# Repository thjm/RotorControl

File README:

$Id: README,v 1.8 2014/03/23 08:37:47 mathes Exp $

README file for Projekte/RotorControl
-----------------------------------------------------------------------------

This is the README file for the rotator controller project.

Directories:
-------------

- Bootloader : contains the boot loeader for the antenna sensor uC

- Docu : various documentation files

- DisplayUR : parts takes from Ulrich Radig's (http://www.ulrichradig.de)
          PowerSupply project. The display unit presented there seems to be
          quite usable for a simple display here, just software needs to be 
          adopted.

- Eagle : contains drawings and schemes done with the Eagle layout program

- Linux : various test programs, to be run on Linux

- LSM303 : library and example for the Pololu LSM303DLH 6-axis sensor
          breakout board. The boards contains a 3-axis magnetometer and a
          3-axis accelerometer.
          See also:
          - http://www.lipoly.de/index.php?main_page=product_info&products_id=165628
          - data sheet LSM303DLH.pdf
          - LSM303DLH-compass-app-note.pdf
          - LSM303DLH-orangutan-example-cde.zip
          - UM10204.pdf (I2C-bus specification)
          - https://github.com/ryantm/LSM303DLH (Arduino library)

- Test : directory containing various test programs for the 'rotorcontrol'
         hardware environment

Project layout (Rev. 1.1)
-------------------------

- the display of UR's PS1 project will be used to display the current and the
  set value for the azimuth (directory DisplayUR)

- a LSM303DLH accelerometer and compass module will be used to determine the
  antenna direction. It will be coupled to the main electronics via a serial
  interface (coupled via RS-485)

- the main electronics module has the task to
  - receive direction information from the LSM303DLH
  - calculate/average the direction information and send it to the display 
    module
  - compare the current direction with the preset value and pass this
    information to the rotator controller (software module)
  - switch the rotator motor in an appropriate way to achieve the desired
    direction; handle (optional) end-switches and a clutch/brake
  - get users input via push buttons (attached to the main electronics or to
    the display module?)
  - ...

=============================================================================

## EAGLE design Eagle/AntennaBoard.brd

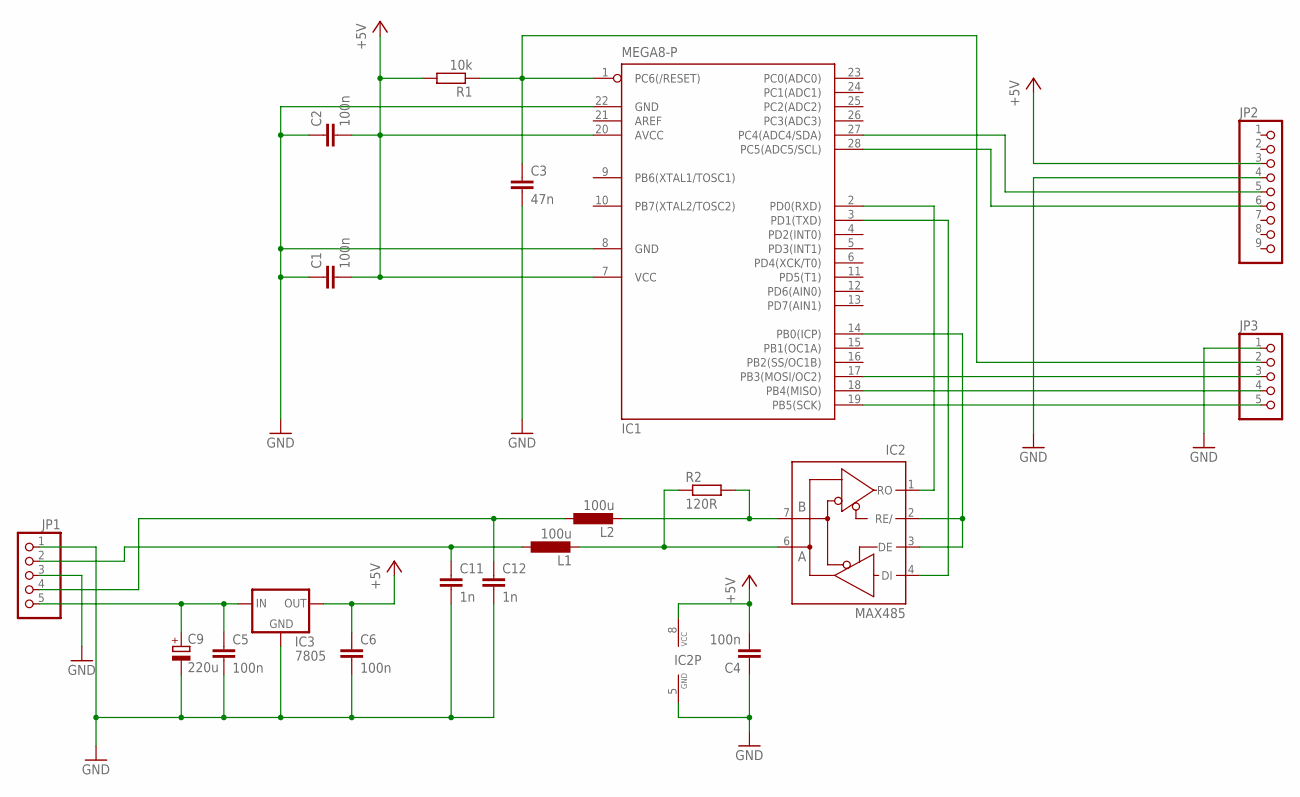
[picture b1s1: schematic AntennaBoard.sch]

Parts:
C1, C2, C4, C5, C6: 100n; C050-024X044
C3: 47n; C050-024X044
C9: 220u; E5-10,5
C11, C12: 1n; C025-024X044
IC1: MEGA8-P; DIL28-3
IC2: MAX485; DIL08
IC3: 7805; 78XXL
JP1: PINHD-1X5/90; 1X05/90
JP2: PINHD-1X9; 1X09
JP3: PINHD-1X5; 1X05
L1, L2: 100u; 0207/12
R1: 10k; 0207/10
R2: 120R; 0207/10

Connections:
+5V: C1.2, C2.2, C4.2, C6.1, IC1.7 (VCC), IC1.20 (AVCC), IC2.8 (VCC), IC3.OUT, JP2.3, R1.2
GND: C1.1, C2.1, C3.2, C4.1, C5.2, C6.2, C9.-, C11.2, C12.2, IC1.8 (GND), IC1.22 (GND), IC2.5 (GND), IC3.GND, JP1.1, JP1.3, JP2.4, JP3.1
unnamed: C5.1, C9.+, IC3.IN, JP1.5
unnamed: IC2.6 (A), L1.2, R2.1
unnamed: C12.1, JP1.4, L2.1
unnamed: IC1.28 (PC5(ADC5/SCL)), JP2.6
unnamed: C3.1, IC1.1 (PC6(/RESET)), JP3.2, R1.1
unnamed: IC1.27 (PC4(ADC4/SDA)), JP2.5
unnamed: IC1.14 (PB0(ICP)), IC2.2 (RE/), IC2.3 (DE)
unnamed: IC1.2 (PD0(RXD)), IC2.1 (RO)
unnamed: IC1.3 (PD1(TXD)), IC2.4 (DI)
unnamed: IC2.7 (B), L2.2, R2.2
unnamed: C11.1, JP1.2, L1.1
unnamed: IC1.17 (PB3(MOSI/OC2)), JP3.3
unnamed: IC1.18 (PB4(MISO)), JP3.4
unnamed: IC1.19 (PB5(SCK)), JP3.5

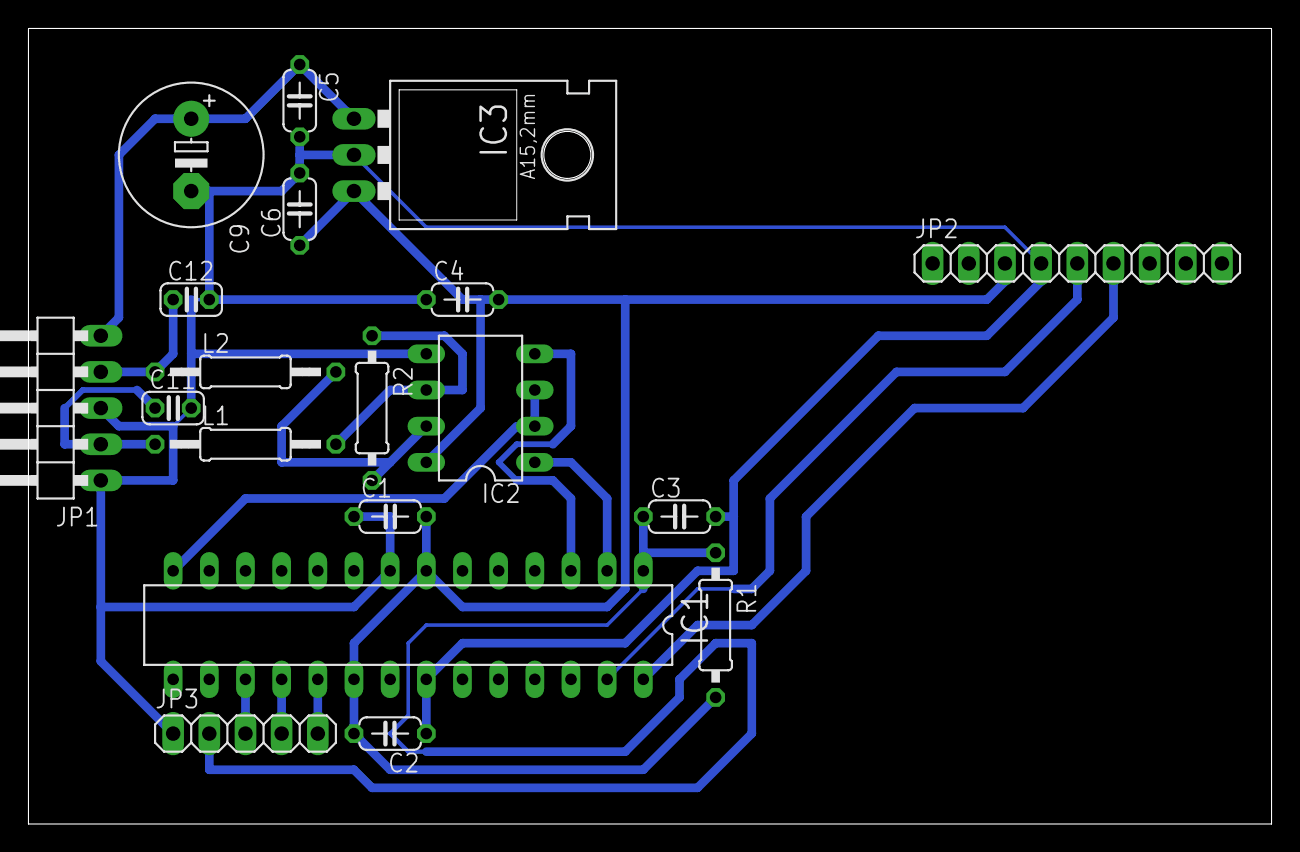
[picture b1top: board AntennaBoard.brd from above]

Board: 2 copper layers, 87.3 x 55.9 mm, 19 parts (0 on the bottom side), 16 nets.

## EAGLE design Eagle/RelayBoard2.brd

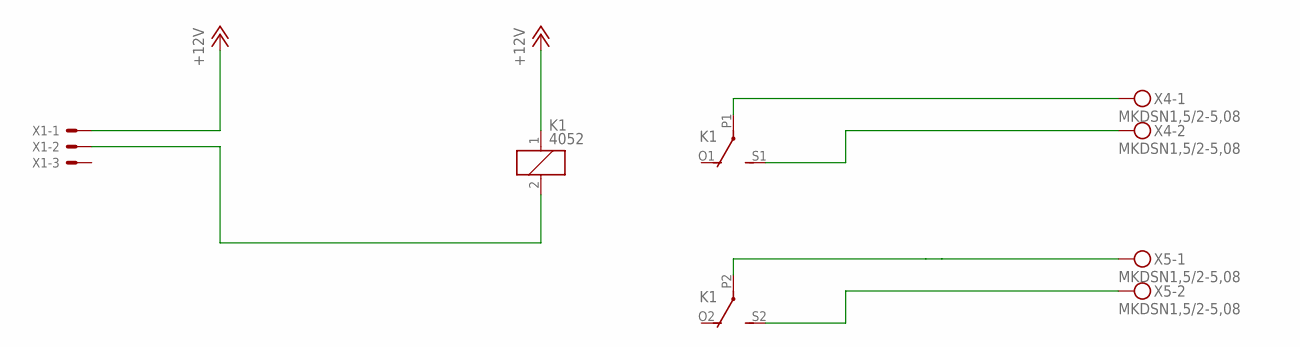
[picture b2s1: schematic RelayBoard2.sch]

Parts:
K1: 4052; F4052
X1: KK-156-3
X4, X5: MKDSN1,5/2-5,08

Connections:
+12V: K1.1, X1.1
unnamed: K1.2, X1.2
unnamed: K1.P2, X5.1
unnamed: K1.S2 (S), X5.2
unnamed: K1.S1 (S), X4.2
unnamed: K1.P1, X4.1

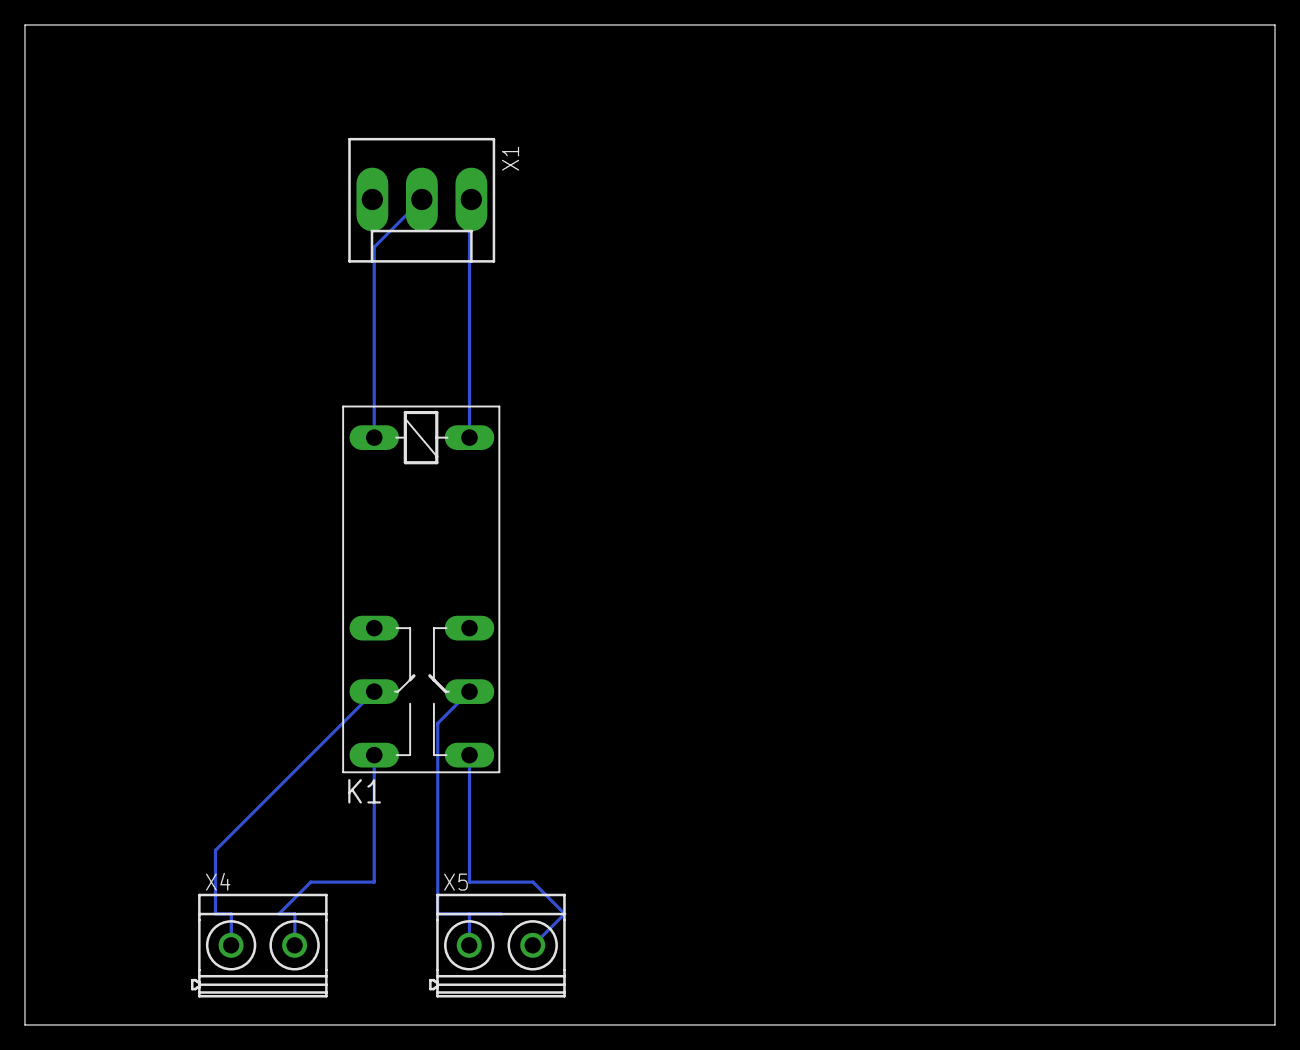
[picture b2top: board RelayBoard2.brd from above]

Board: 2 copper layers, 100.0 x 80.0 mm, 4 parts (0 on the bottom side), 6 nets.

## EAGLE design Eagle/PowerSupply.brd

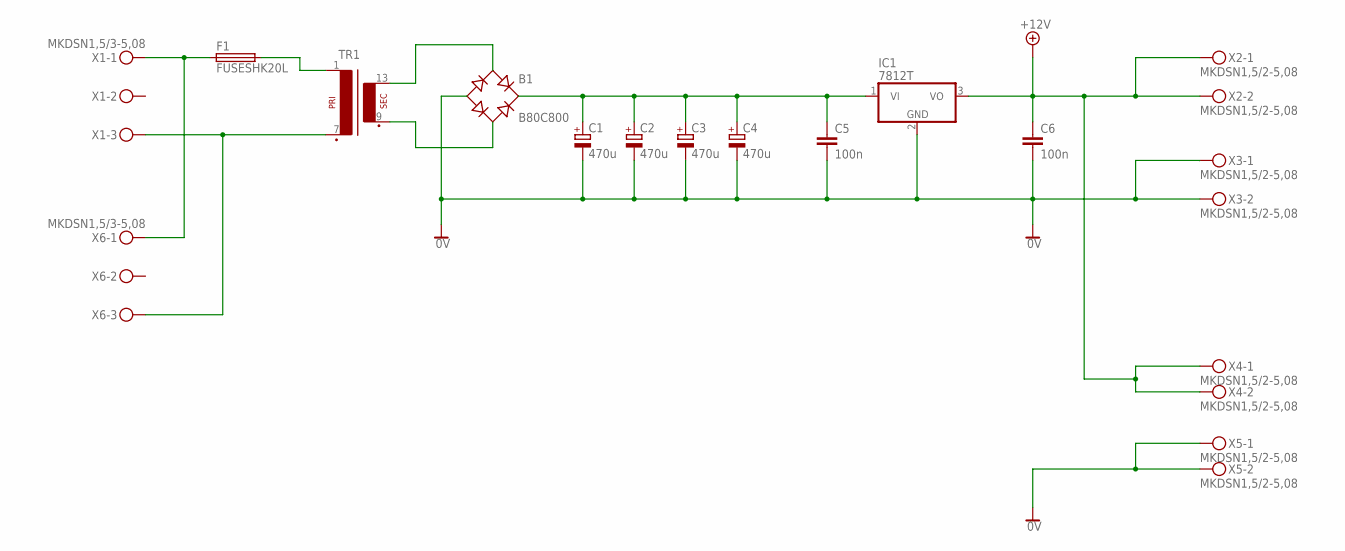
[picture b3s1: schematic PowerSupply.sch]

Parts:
B1: B80C800; B-DIL
C1, C2, C3, C4: 470u; E5-10,5
C5, C6: 100n; C050-024X044
F1: FUSESHK20L; SHK20L
IC1: 7812T; TO220H
TR1: EI54-1B
X1: MKDSN1,5/3-5,08
X2, X3, X4, X5: MKDSN1,5/2-5,08
X6: MKDSN1,5/3-5,08; MPN SMKDSN1,5/3-5,08

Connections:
0V: B1.-, C1.-, C2.-, C3.-, C4.-, C5.2, C6.2, IC1.2 (GND), X3.1, X3.2, X5.1, X5.2
+12V: C6.1, IC1.3 (VO), X2.1, X2.2, X4.1, X4.2
unnamed: F1.1A (1), X1.1, X6.1
unnamed: F1.2A (2), TR1.1
unnamed: B1.AC1, TR1.13 (S4)
unnamed: B1.AC2, TR1.9 (S3)
unnamed: B1.+, C1.+, C2.+, C3.+, C4.+, C5.1, IC1.1 (VI)
unnamed: TR1.7 (P2), X1.3, X6.3

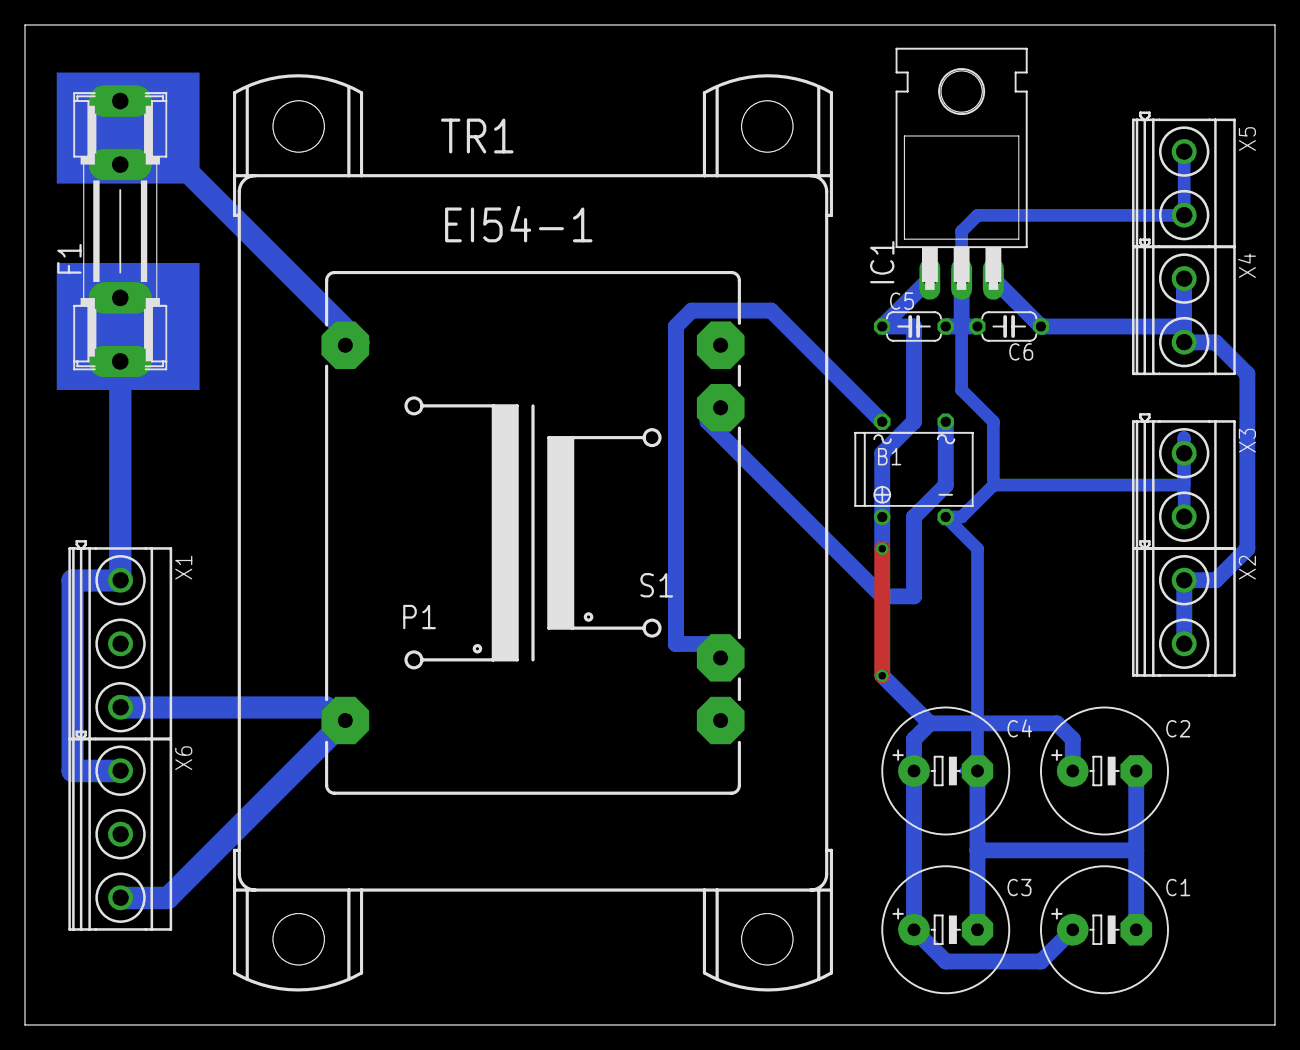
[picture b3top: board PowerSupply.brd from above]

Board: 2 copper layers, 100.0 x 80.0 mm, 16 parts (0 on the bottom side), 8 nets.

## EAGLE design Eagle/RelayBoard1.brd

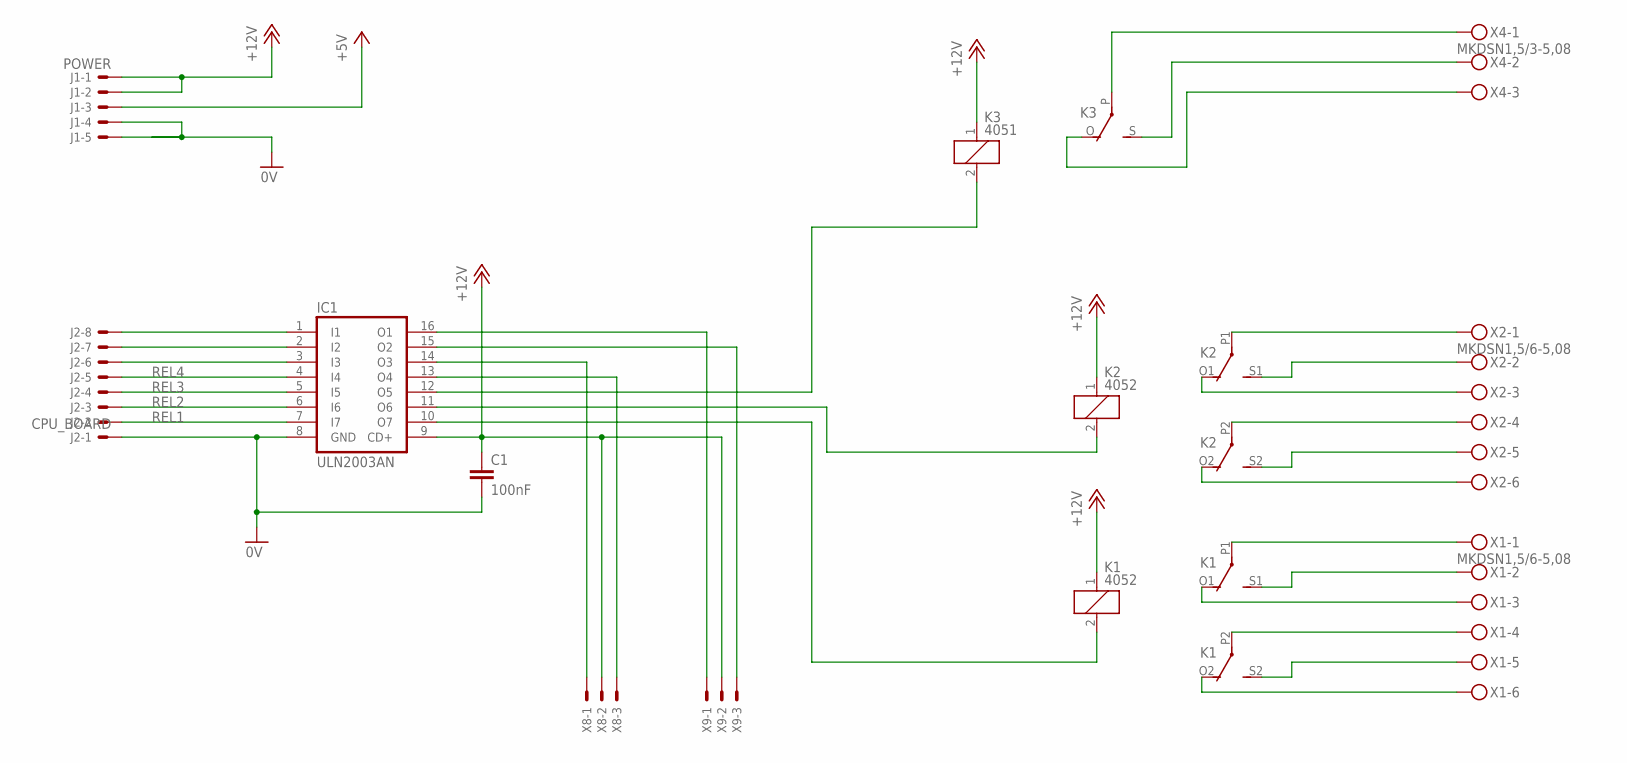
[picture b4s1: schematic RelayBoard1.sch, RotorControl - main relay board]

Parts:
C1: 100nF; C025-025X050
IC1: ULN2003AN; DIL16
J1: POWER; 6410-05
J2: CPU_BOARD; 6410-08
K1, K2: 4052; F4052
K3: 4051; G2R
X1, X2: MKDSN1,5/6-5,08
X4: MKDSN1,5/3-5,08; MPN SMKDSN1,5/3-5,08
X8, X9: KK-156-3

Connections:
0V: C1.2, IC1.8 (GND), J1.4, J1.5, J2.1
+5V: J1.3
+12V: C1.1, IC1.9 (CD+), J1.1, J1.2, K1.1, K2.1, K3.1, X8.2, X9.2
unnamed: K3.P, X4.1
unnamed: K3.S, X4.2
unnamed: K3.O, X4.3
unnamed: IC1.10 (O7), K1.2
unnamed: K2.P1, X2.1
unnamed: K2.S1 (S), X2.2
unnamed: K2.O1 (O), X2.3
unnamed: K2.P2, X2.4
unnamed: K2.S2 (S), X2.5
unnamed: K2.O2 (O), X2.6
unnamed: K1.P1, X1.1
unnamed: K1.S1 (S), X1.2
unnamed: K1.O1 (O), X1.3
unnamed: K1.P2, X1.4
unnamed: K1.S2 (S), X1.5
unnamed: K1.O2 (O), X1.6
unnamed: IC1.3 (I3), J2.6
unnamed: IC1.2 (I2), J2.7
unnamed: IC1.1 (I1), J2.8
unnamed: IC1.11 (O6), K2.2
unnamed: IC1.12 (O5), K3.2
unnamed: IC1.14 (O3), X8.1
unnamed: IC1.13 (O4), X8.3
unnamed: IC1.16 (O1), X9.1
unnamed: IC1.15 (O2), X9.3
REL1: IC1.7 (I7), J2.2
REL2: IC1.6 (I6), J2.3
REL3: IC1.5 (I5), J2.4
REL4: IC1.4 (I4), J2.5

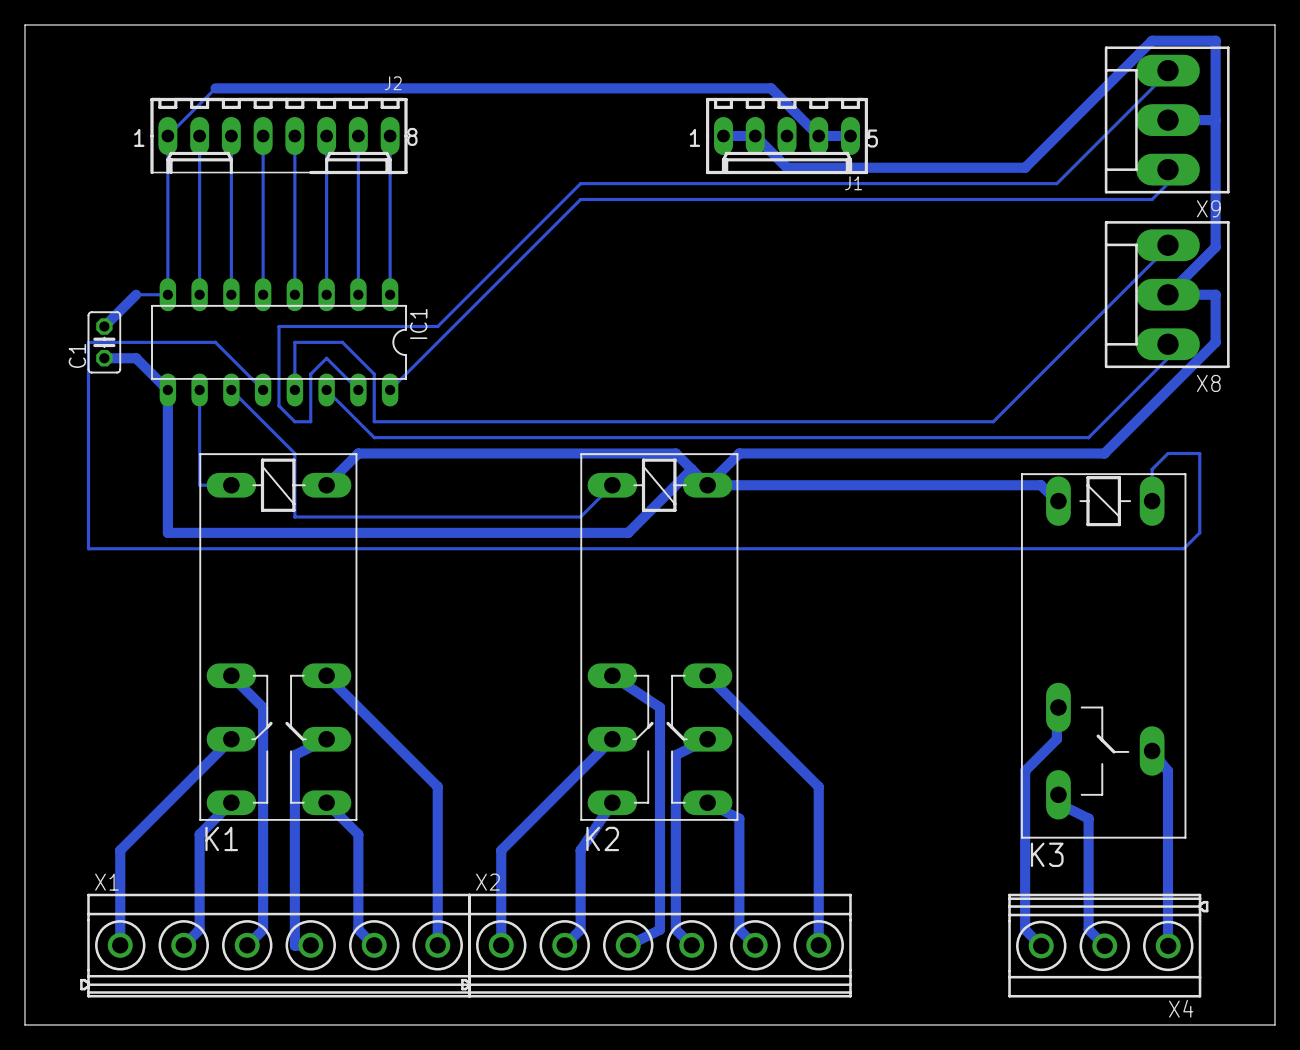
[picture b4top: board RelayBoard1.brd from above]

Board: 2 copper layers, 100.0 x 80.0 mm, 12 parts (0 on the bottom side), 31 nets.

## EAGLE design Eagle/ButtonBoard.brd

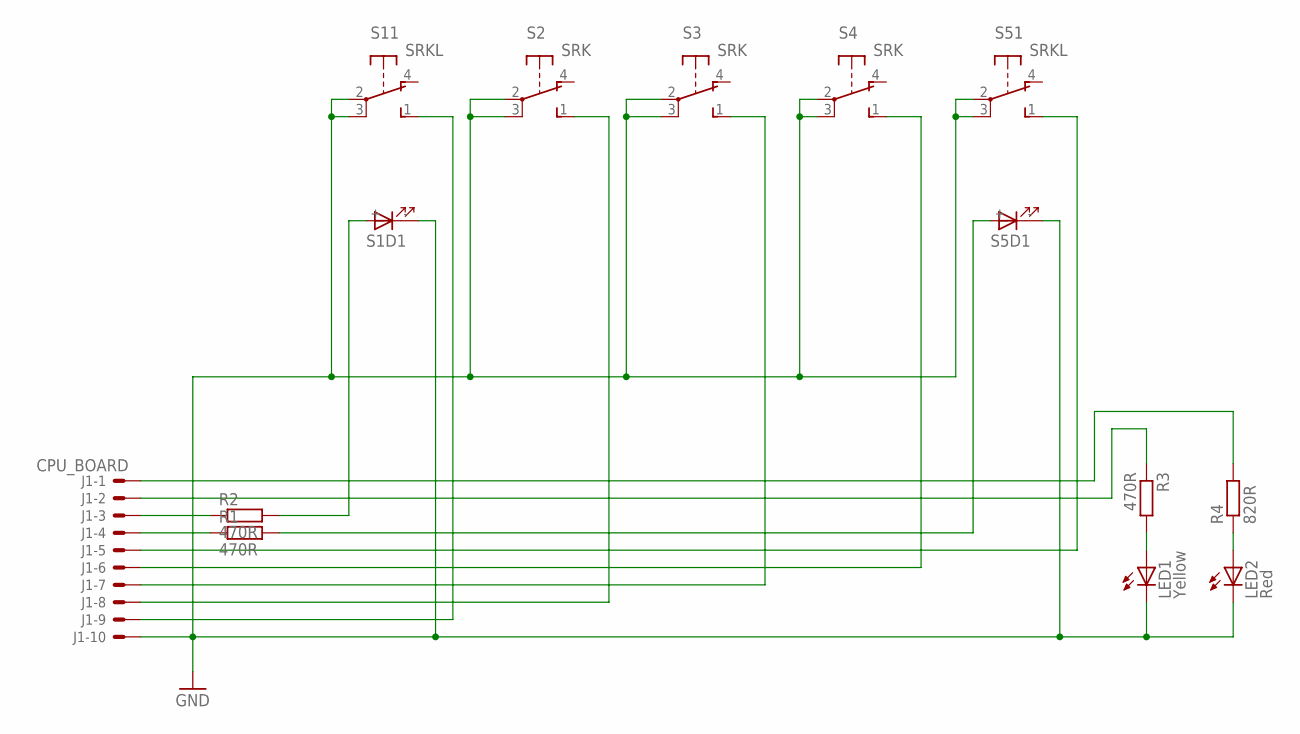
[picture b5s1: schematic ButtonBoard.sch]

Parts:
J1: CPU_BOARD; 7395-10
LED1: Yellow; LED3MM
LED2: Red; LED3MM
R1, R2, R3: 470R; 0207/10
R4: 820R; 0207/10
S1, S5: SRKL
S2, S3, S4: SRK

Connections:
GND: J1.10, LED1.K (C), LED2.K (C), S1.2, S1.3, S1.- (C), S2.2, S2.3, S3.2, S3.3, S4.2, S4.3, S5.2, S5.3, S5.- (C)
unnamed: R2.2, S1.+ (A)
unnamed: J1.3, R2.1
unnamed: J1.4, R1.1
unnamed: J1.9, S1.1 (S)
unnamed: R1.2, S5.+ (A)
unnamed: J1.8, S2.1 (S)
unnamed: J1.7, S3.1 (S)
unnamed: J1.6, S4.1 (S)
unnamed: J1.5, S5.1 (S)
unnamed: LED2.A, R4.1
unnamed: LED1.A, R3.2
unnamed: J1.2, R3.1
unnamed: J1.1, R4.2

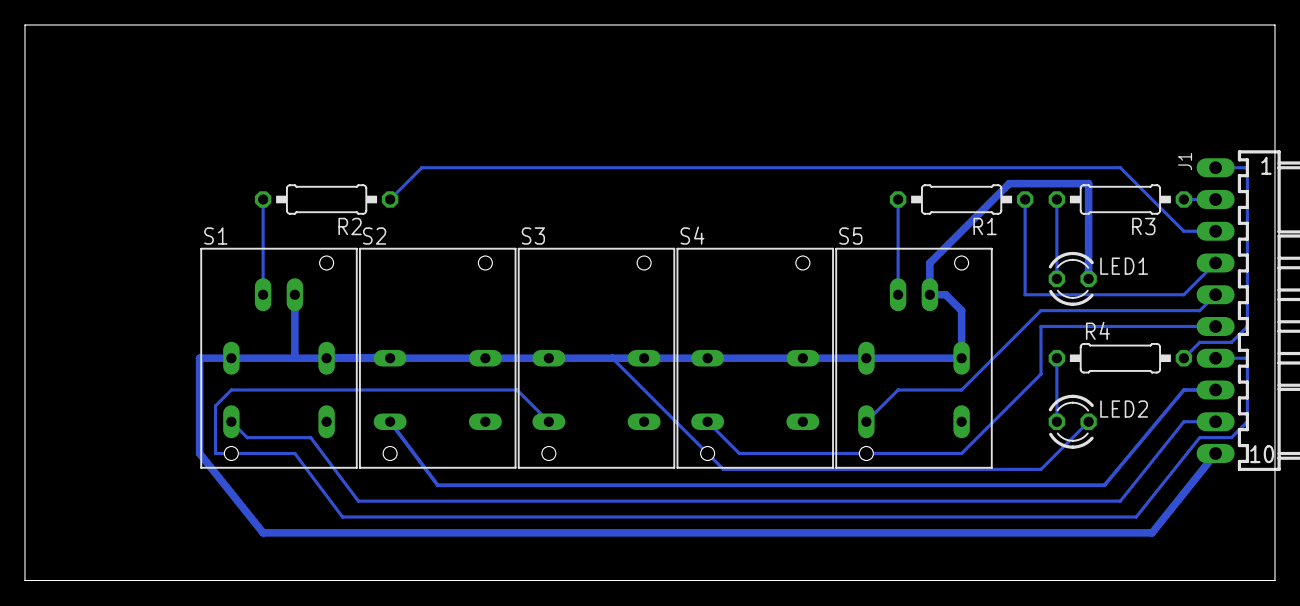
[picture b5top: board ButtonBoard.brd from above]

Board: 2 copper layers, 100.0 x 44.4 mm, 12 parts (0 on the bottom side), 14 nets.

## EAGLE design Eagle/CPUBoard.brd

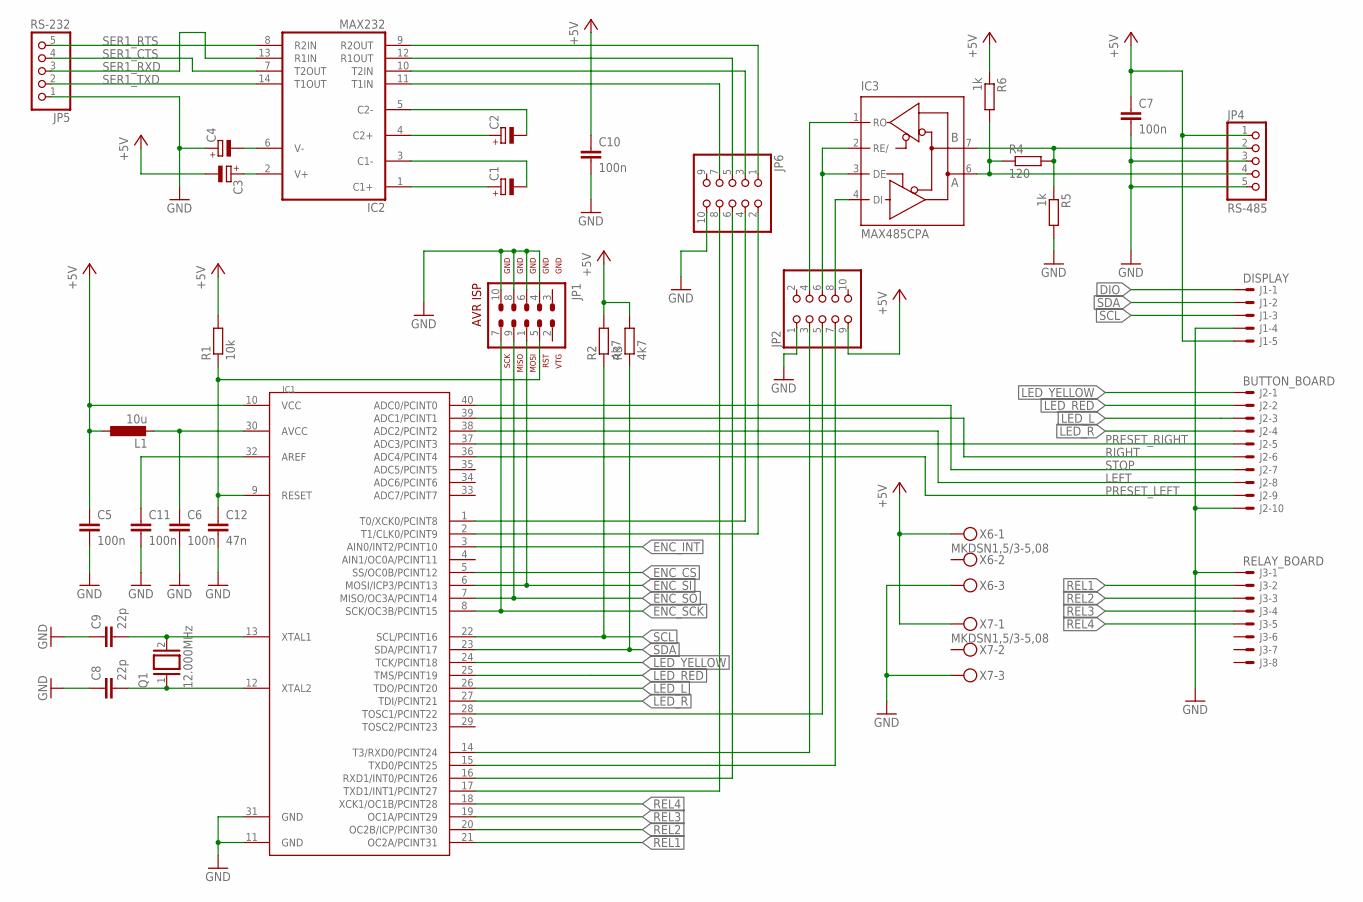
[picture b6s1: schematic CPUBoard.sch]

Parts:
C1, C2, C3, C4: CPOL-EUE2,5-6E; E2,5-6E
C5, C6, C7, C10, C11: 100n; C025-025X050
C8, C9: 22p; C025-024X044
C12: 47n; C025-025X050
IC1: MEGA1284P; DIL40
IC2: MAX232; DIL16
IC3: MAX485CPA; DIL08
J1: DISPLAY; 6410-05
J2: BUTTON_BOARD; 6410-10
J3: RELAY_BOARD; 6410-08
JP1: AVR-ISP-10
JP2, JP6: PINHD-2X5; 2X05
JP4: RS-485; 1X05
JP5: RS-232; 1X05
L1: 10u; 0207/10
Q1: 12.000MHz; QS
R1: 10k; 0207/10
R2, R3: 4k7; 0207/10
R4: 120; 0207/10
R5, R6: 1k; 0207/10
X6, X7: MKDSN1,5/3-5,08

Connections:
+5V: C3.-, C5.1, C7.1, C10.1, IC1.10 (VCC), J1.5, JP2.9, JP4.1, L1.1, R1.2, R2.2, R3.2, R6.1, X6.1, X7.1
DIO: J1.1
ENC_CS: IC1.5 (SS/OC0B/PCINT12)
ENC_INT: IC1.3 (AIN0/INT2/PCINT10)
ENC_SCK: IC1.8 (SCK/OC3B/PCINT15), JP1.7
ENC_SI: IC1.6 (MOSI/ICP3/PCINT13), JP1.1
ENC_SO: IC1.7 (MISO/OC3A/PCINT14), JP1.9
GND: C4.+, C5.2, C6.2, C7.2, C8.1, C9.1, C10.2, C11.2, C12.2, IC1.11 (GND), IC1.31 (GND), IC2.15 (GND), IC3.5 (GND), J1.4, J2.10, J3.1, JP1.4, JP1.6, JP1.8, JP1.10, JP2.1, JP4.3, JP4.5, JP5.1, JP6.10, R5.2, X6.3, X7.3
LED_L: IC1.26 (TDO/PCINT20), J2.3
LED_R: IC1.27 (TDI/PCINT21), J2.4
LED_RED: IC1.25 (TMS/PCINT19), J2.2
LED_YELLOW: IC1.24 (TCK/PCINT18), J2.1
LEFT: IC1.38 (ADC2/PCINT2), J2.8
unnamed: C9.2, IC1.13 (XTAL1), Q1.2
unnamed: C8.2, IC1.12 (XTAL2), Q1.1
unnamed: C12.1, IC1.9 (RESET), JP1.5, R1.1
unnamed: IC2.11 (T1IN), JP6.7
unnamed: C1.+, IC2.1 (C1+)
unnamed: C1.-, IC2.3 (C1-)
unnamed: C2.+, IC2.4 (C2+)
unnamed: C2.-, IC2.5 (C2-)
unnamed: C3.+, IC2.2 (V+)
unnamed: C4.-, IC2.6 (V-)
unnamed: IC2.12 (R1OUT), JP6.5
unnamed: C6.1, IC1.30 (AVCC), L1.2
unnamed: IC1.14 (T3/RXD0/PCINT24), JP2.3
unnamed: IC1.15 (TXD0/PCINT25), JP2.7
unnamed: IC1.28 (TOSC1/PCINT22), JP2.5
unnamed: IC1.1 (T0/XCK0/PCINT8), JP6.4
unnamed: IC3.6 (A), JP4.4, R4.1, R6.2
unnamed: IC3.7 (B), JP4.2, R4.2, R5.1
unnamed: C11.1, IC1.32 (AREF)
unnamed: IC3.2 (RE/), IC3.3 (DE), JP2.6
unnamed: IC3.4 (DI), JP2.8
unnamed: IC1.16 (RXD1/INT0/PCINT26), JP6.6
unnamed: IC3.1 (RO), JP2.4
unnamed: IC1.17 (TXD1/INT1/PCINT27), JP6.8
unnamed: IC1.2 (T1/CLK0/PCINT9), JP6.2
unnamed: IC2.9 (R2OUT), JP6.1
unnamed: IC2.10 (T2IN), JP6.3
PRESET_LEFT: IC1.36 (ADC4/PCINT4), J2.9
PRESET_RIGHT: IC1.37 (ADC3/PCINT3), J2.5
REL1: IC1.21 (OC2A/PCINT31), J3.2
REL2: IC1.20 (OC2B/ICP/PCINT30), J3.3
REL3: IC1.19 (OC1A/PCINT29), J3.4
REL4: IC1.18 (XCK1/OC1B/PCINT28), J3.5
RIGHT: IC1.39 (ADC1/PCINT1), J2.6
SCL: IC1.22 (SCL/PCINT16), J1.3, R2.1
SDA: IC1.23 (SDA/PCINT17), J1.2, R3.1
SER1_CTS: IC2.13 (R1IN), JP5.3
SER1_RTS: IC2.8 (R2IN), JP5.5
SER1_RXD: IC2.7 (T2OUT), JP5.4
SER1_TXD: IC2.14 (T1OUT), JP5.2
STOP: IC1.40 (ADC0/PCINT0), J2.7
VCC: IC2.16 (VCC), IC3.8 (VCC)

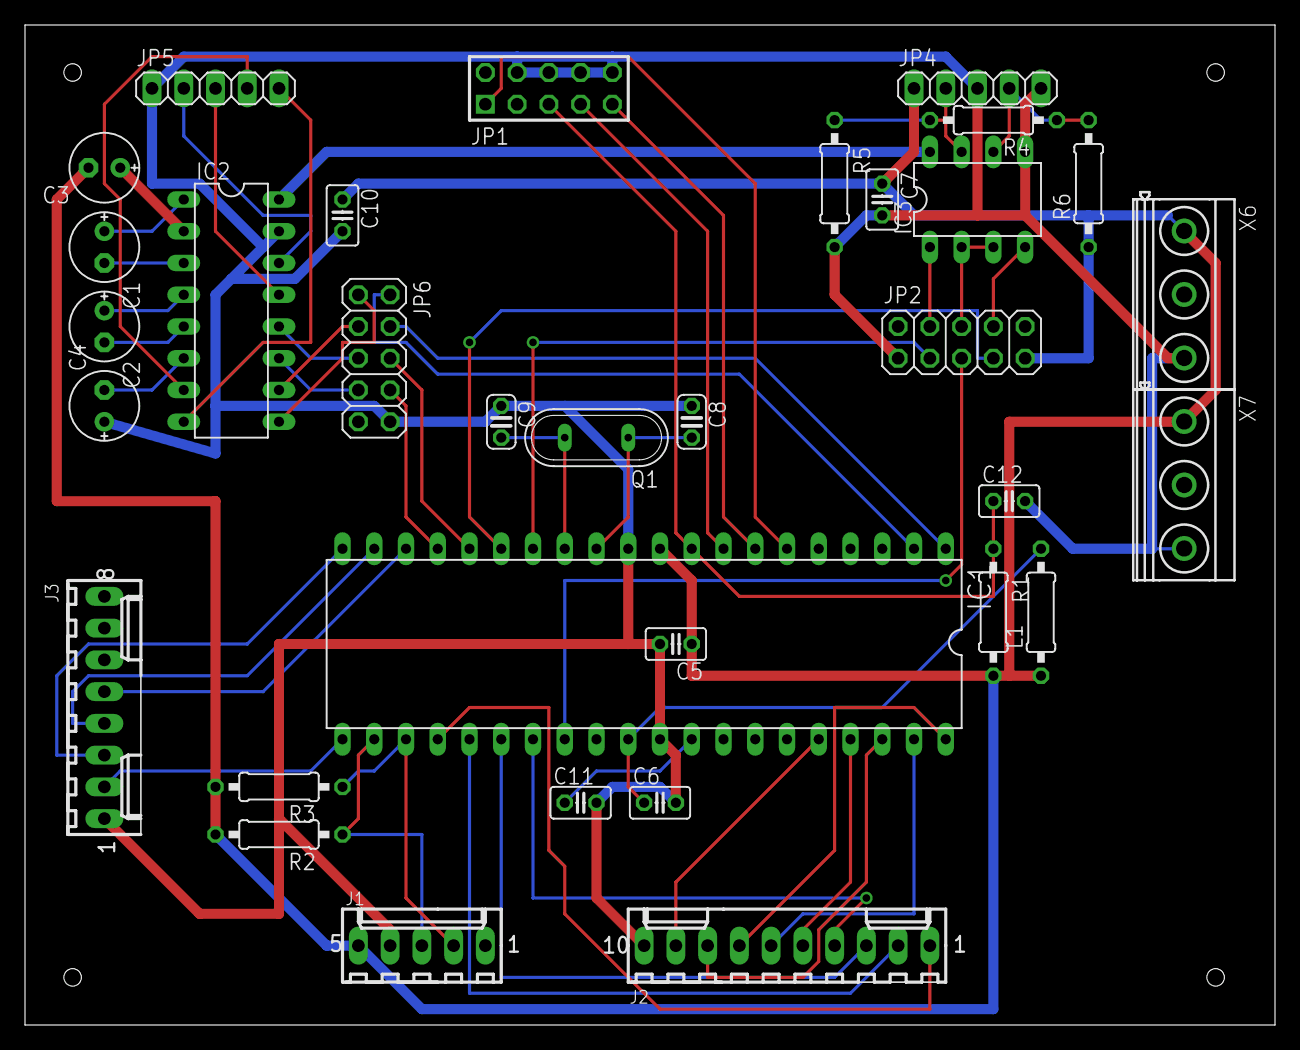
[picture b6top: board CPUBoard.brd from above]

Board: 2 copper layers, 100.0 x 80.0 mm, 33 parts (0 on the bottom side), 52 nets.

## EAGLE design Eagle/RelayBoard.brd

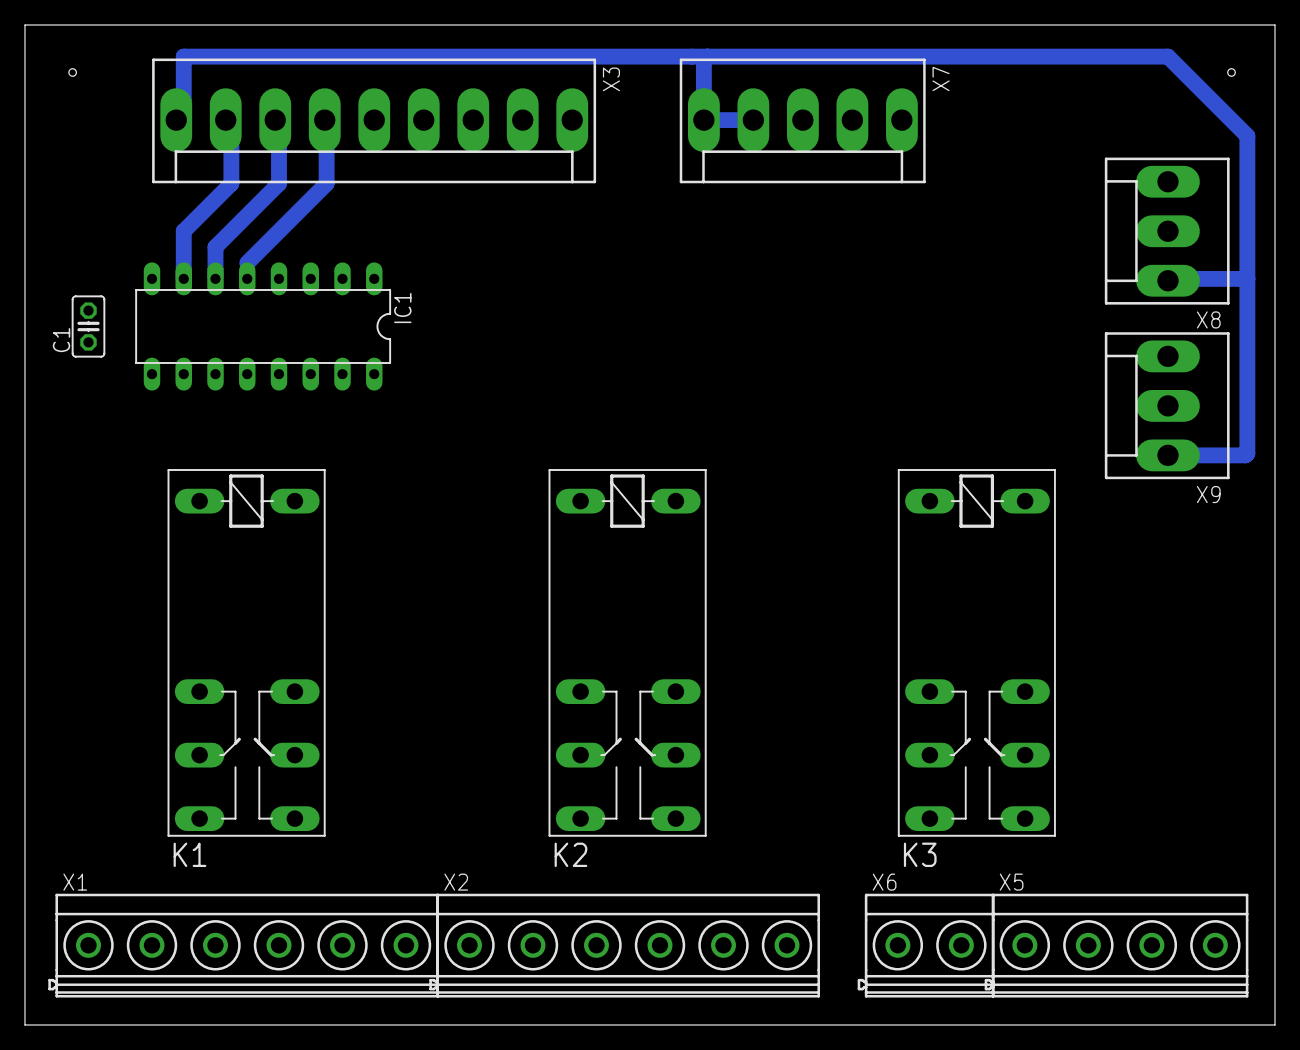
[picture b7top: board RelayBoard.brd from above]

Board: 2 copper layers, 100.0 x 80.0 mm, 13 parts (0 on the bottom side), 33 nets.

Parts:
C1: 100nF; C025-025X050
IC1: ULN2003AN; DIL16
K1, K2, K3: 4052; F4052
X1, X2: MKDSN1,5/6-5,08
X3: Con1; KK-156-9
X5: MKDSN1,5/4-5,08
X6: MKDSN1,5/2-5,08
X7: Con2; KK-156-5
X8, X9: KK-156-3

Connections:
0V: C1.2, IC1.8, X3.9, X7.4, X7.5, X8.1, X9.1
+5V: X3.1, X7.3
+12V: C1.1, IC1.9, K1.1, K2.1, K3.1, X7.1, X7.2
unnamed: K3.P1, X6.1
unnamed: K3.P2, X6.2
unnamed: K3.S1, X5.1, X5.2
unnamed: IC1.16, K3.2
unnamed: K3.S2, X5.3, X5.4
unnamed: K2.P1, X2.1
unnamed: K2.S1, X2.2
unnamed: K2.O1, X2.3
unnamed: K2.P2, X2.4
unnamed: K2.S2, X2.5
unnamed: K2.O2, X2.6
unnamed: K1.P1, X1.1
unnamed: K1.S1, X1.2
unnamed: K1.O1, X1.3
unnamed: K1.P2, X1.4
unnamed: K1.S2, X1.5
unnamed: K1.O2, X1.6
unnamed: IC1.1, X3.2
unnamed: IC1.2, X3.3
unnamed: IC1.3, X3.4
unnamed: IC1.4, X3.5
unnamed: IC1.5, X3.6
unnamed: IC1.6, X3.7
unnamed: IC1.7, X3.8
unnamed: IC1.15, K2.2
unnamed: IC1.14, K1.2
unnamed: IC1.11, X8.3
unnamed: IC1.10, X8.2
unnamed: IC1.13, X9.3
unnamed: IC1.12, X9.2
